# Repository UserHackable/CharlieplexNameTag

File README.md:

## CharlieplexNameTag 

### Board dimensions

* (310000, 240000) original units
* (3.1000, 2.4000) inches
* (78.7400, 60.9600) mm

| Front | Back |
| --- | --- |
|  |  |

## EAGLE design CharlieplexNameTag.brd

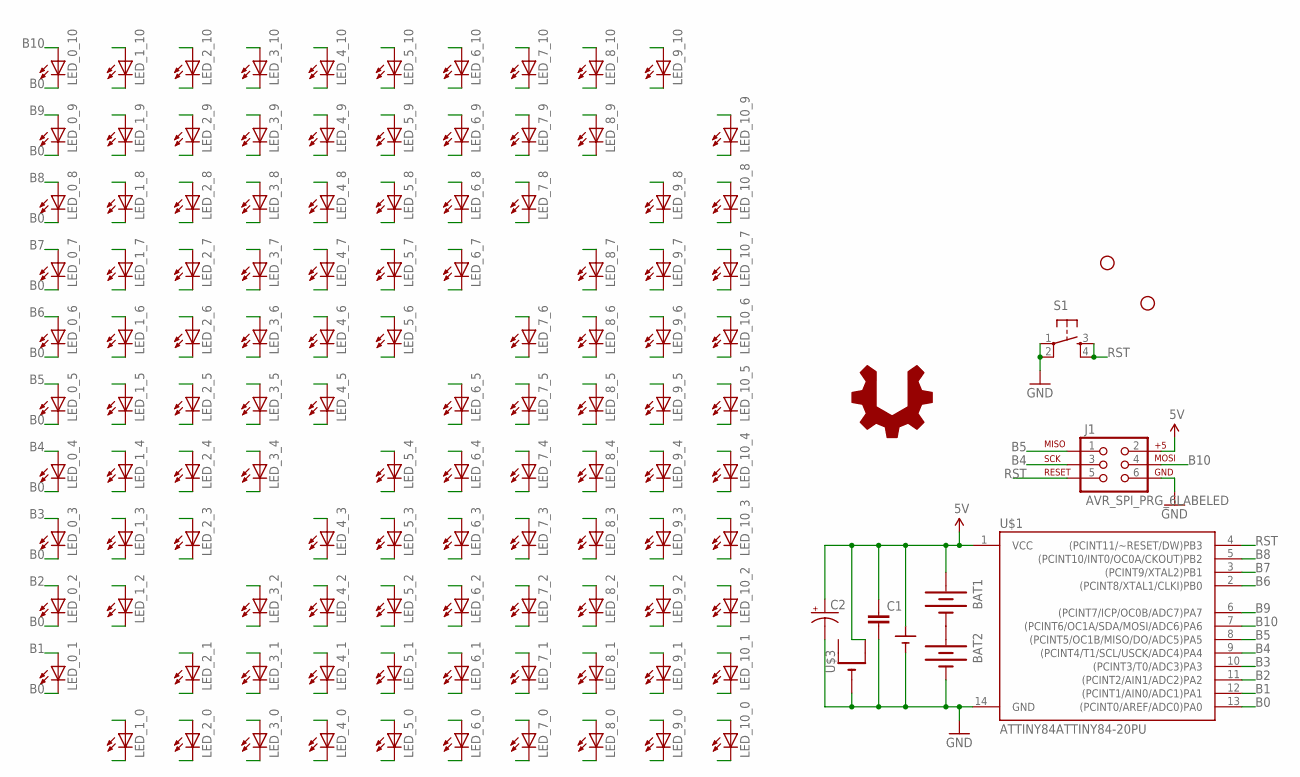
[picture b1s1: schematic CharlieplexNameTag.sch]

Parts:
BAT1, BAT2: BATTERYAAA; BATTERY-AAA
C1: CAPPTH; CAP-PTH-SMALL
C2: CAP_POLPTH1; CPOL-RADIAL-100UF-25V
J1: AVR_SPI_PRG_6LABELED; 2X3-NS
LED_0_1, LED_0_2, LED_0_3, LED_0_4, LED_0_5, LED_0_6, LED_0_7, LED_0_8, LED_0_9, LED_0_10, LED_1_0, LED_1_2, LED_1_3, LED_1_4, LED_1_5, LED_1_6, LED_1_7, LED_1_8, LED_1_9, LED_1_10, LED_2_0, LED_2_1, LED_2_3, LED_2_4, LED_2_5, LED_2_6, LED_2_7, LED_2_8, LED_2_9, LED_2_10, LED_3_0, LED_3_1, LED_3_2, LED_3_4, LED_3_5, LED_3_6, LED_3_7, LED_3_8, LED_3_9, LED_3_10, LED_4_0, LED_4_1, LED_4_2, LED_4_3, LED_4_5, LED_4_6, LED_4_7, LED_4_8, LED_4_9, LED_4_10, LED_5_0, LED_5_1, LED_5_2, LED_5_3, LED_5_4, LED_5_6, LED_5_7, LED_5_8, LED_5_9, LED_5_10, LED_6_0, LED_6_1, LED_6_2, LED_6_3, LED_6_4, LED_6_5, LED_6_7, LED_6_8, LED_6_9, LED_6_10, LED_7_0, LED_7_1, LED_7_2, LED_7_3, LED_7_4, LED_7_5, LED_7_6, LED_7_8, LED_7_9, LED_7_10, LED_8_0, LED_8_1, LED_8_2, LED_8_3, LED_8_4, LED_8_5, LED_8_6, LED_8_7, LED_8_9, LED_8_10, LED_9_0, LED_9_1, LED_9_2, LED_9_3, LED_9_4, LED_9_5, LED_9_6, LED_9_7, LED_9_8, LED_9_10, LED_10_0, LED_10_1, LED_10_2, LED_10_3, LED_10_4, LED_10_5, LED_10_6, LED_10_7, LED_10_8, LED_10_9: LEDOVAL; LED-OVAL
S1: TAC_SWITCHPTH; TACTILE-PTH
STANDOFF1, STANDOFF4: STAND-OFF
U$1: ATTINY84ATTINY84-20PU; DIL14
U$2: BATT2AAA; BC2AAAPC
U$3: CR2032THM; CR2032-THRU
U$4: USER_HACKABLE

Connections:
5V: BAT1.PWR@1 (+), C1.1, C2.1 (+), J1.2 (V+), U$1.1 (VCC), U$2.+, U$3.+2 (+1)
B0: LED_0_1.CATHODE (C), LED_0_2.CATHODE (C), LED_0_3.CATHODE (C), LED_0_4.CATHODE (C), LED_0_5.CATHODE (C), LED_0_6.CATHODE (C), LED_0_7.CATHODE (C), LED_0_8.CATHODE (C), LED_0_9.CATHODE (C), LED_0_10.CATHODE (C), LED_1_0.ANODE (A), LED_2_0.ANODE (A), LED_3_0.ANODE (A), LED_4_0.ANODE (A), LED_5_0.ANODE (A), LED_6_0.ANODE (A), LED_7_0.ANODE (A), LED_8_0.ANODE (A), LED_9_0.ANODE (A), LED_10_0.ANODE (A), U$1.13 ((PCINT0/AREF/ADC0)PA0)
B1: LED_0_1.ANODE (A), LED_1_0.CATHODE (C), LED_1_2.CATHODE (C), LED_1_3.CATHODE (C), LED_1_4.CATHODE (C), LED_1_5.CATHODE (C), LED_1_6.CATHODE (C), LED_1_7.CATHODE (C), LED_1_8.CATHODE (C), LED_1_9.CATHODE (C), LED_1_10.CATHODE (C), LED_2_1.ANODE (A), LED_3_1.ANODE (A), LED_4_1.ANODE (A), LED_5_1.ANODE (A), LED_6_1.ANODE (A), LED_7_1.ANODE (A), LED_8_1.ANODE (A), LED_9_1.ANODE (A), LED_10_1.ANODE (A), U$1.12 ((PCINT1/AIN0/ADC1)PA1)
B2: LED_0_2.ANODE (A), LED_1_2.ANODE (A), LED_2_0.CATHODE (C), LED_2_1.CATHODE (C), LED_2_3.CATHODE (C), LED_2_4.CATHODE (C), LED_2_5.CATHODE (C), LED_2_6.CATHODE (C), LED_2_7.CATHODE (C), LED_2_8.CATHODE (C), LED_2_9.CATHODE (C), LED_2_10.CATHODE (C), LED_3_2.ANODE (A), LED_4_2.ANODE (A), LED_5_2.ANODE (A), LED_6_2.ANODE (A), LED_7_2.ANODE (A), LED_8_2.ANODE (A), LED_9_2.ANODE (A), LED_10_2.ANODE (A), U$1.11 ((PCINT2/AIN1/ADC2)PA2)
B3: LED_0_3.ANODE (A), LED_1_3.ANODE (A), LED_2_3.ANODE (A), LED_3_0.CATHODE (C), LED_3_1.CATHODE (C), LED_3_2.CATHODE (C), LED_3_4.CATHODE (C), LED_3_5.CATHODE (C), LED_3_6.CATHODE (C), LED_3_7.CATHODE (C), LED_3_8.CATHODE (C), LED_3_9.CATHODE (C), LED_3_10.CATHODE (C), LED_4_3.ANODE (A), LED_5_3.ANODE (A), LED_6_3.ANODE (A), LED_7_3.ANODE (A), LED_8_3.ANODE (A), LED_9_3.ANODE (A), LED_10_3.ANODE (A), U$1.10 ((PCINT3/T0/ADC3)PA3)
B4: J1.3 (SCK), LED_0_4.ANODE (A), LED_1_4.ANODE (A), LED_2_4.ANODE (A), LED_3_4.ANODE (A), LED_4_0.CATHODE (C), LED_4_1.CATHODE (C), LED_4_2.CATHODE (C), LED_4_3.CATHODE (C), LED_4_5.CATHODE (C), LED_4_6.CATHODE (C), LED_4_7.CATHODE (C), LED_4_8.CATHODE (C), LED_4_9.CATHODE (C), LED_4_10.CATHODE (C), LED_5_4.ANODE (A), LED_6_4.ANODE (A), LED_7_4.ANODE (A), LED_8_4.ANODE (A), LED_9_4.ANODE (A), LED_10_4.ANODE (A), U$1.9 ((PCINT4/T1/SCL/USCK/ADC4)PA4)
B5: J1.1 (MISO), LED_0_5.ANODE (A), LED_1_5.ANODE (A), LED_2_5.ANODE (A), LED_3_5.ANODE (A), LED_4_5.ANODE (A), LED_5_0.CATHODE (C), LED_5_1.CATHODE (C), LED_5_2.CATHODE (C), LED_5_3.CATHODE (C), LED_5_4.CATHODE (C), LED_5_6.CATHODE (C), LED_5_7.CATHODE (C), LED_5_8.CATHODE (C), LED_5_9.CATHODE (C), LED_5_10.CATHODE (C), LED_6_5.ANODE (A), LED_7_5.ANODE (A), LED_8_5.ANODE (A), LED_9_5.ANODE (A), LED_10_5.ANODE (A), U$1.8 ((PCINT5/OC1B/MISO/DO/ADC5)PA5)
B6: LED_0_6.ANODE (A), LED_1_6.ANODE (A), LED_2_6.ANODE (A), LED_3_6.ANODE (A), LED_4_6.ANODE (A), LED_5_6.ANODE (A), LED_6_0.CATHODE (C), LED_6_1.CATHODE (C), LED_6_2.CATHODE (C), LED_6_3.CATHODE (C), LED_6_4.CATHODE (C), LED_6_5.CATHODE (C), LED_6_7.CATHODE (C), LED_6_8.CATHODE (C), LED_6_9.CATHODE (C), LED_6_10.CATHODE (C), LED_7_6.ANODE (A), LED_8_6.ANODE (A), LED_9_6.ANODE (A), LED_10_6.ANODE (A), U$1.2 ((PCINT8/XTAL1/CLKI)PB0)
B7: LED_0_7.ANODE (A), LED_1_7.ANODE (A), LED_2_7.ANODE (A), LED_3_7.ANODE (A), LED_4_7.ANODE (A), LED_5_7.ANODE (A), LED_6_7.ANODE (A), LED_7_0.CATHODE (C), LED_7_1.CATHODE (C), LED_7_2.CATHODE (C), LED_7_3.CATHODE (C), LED_7_4.CATHODE (C), LED_7_5.CATHODE (C), LED_7_6.CATHODE (C), LED_7_8.CATHODE (C), LED_7_9.CATHODE (C), LED_7_10.CATHODE (C), LED_8_7.ANODE (A), LED_9_7.ANODE (A), LED_10_7.ANODE (A), U$1.3 ((PCINT9/XTAL2)PB1)
B8: LED_0_8.ANODE (A), LED_1_8.ANODE (A), LED_2_8.ANODE (A), LED_3_8.ANODE (A), LED_4_8.ANODE (A), LED_5_8.ANODE (A), LED_6_8.ANODE (A), LED_7_8.ANODE (A), LED_8_0.CATHODE (C), LED_8_1.CATHODE (C), LED_8_2.CATHODE (C), LED_8_3.CATHODE (C), LED_8_4.CATHODE (C), LED_8_5.CATHODE (C), LED_8_6.CATHODE (C), LED_8_7.CATHODE (C), LED_8_9.CATHODE (C), LED_8_10.CATHODE (C), LED_9_8.ANODE (A), LED_10_8.ANODE (A), U$1.5 ((PCINT10/INT0/OC0A/CKOUT)PB2)
B9: LED_0_9.ANODE (A), LED_1_9.ANODE (A), LED_2_9.ANODE (A), LED_3_9.ANODE (A), LED_4_9.ANODE (A), LED_5_9.ANODE (A), LED_6_9.ANODE (A), LED_7_9.ANODE (A), LED_8_9.ANODE (A), LED_9_0.CATHODE (C), LED_9_1.CATHODE (C), LED_9_2.CATHODE (C), LED_9_3.CATHODE (C), LED_9_4.CATHODE (C), LED_9_5.CATHODE (C), LED_9_6.CATHODE (C), LED_9_7.CATHODE (C), LED_9_8.CATHODE (C), LED_9_10.CATHODE (C), LED_10_9.ANODE (A), U$1.6 ((PCINT7/ICP/OC0B/ADC7)PA7)
B10: J1.4 (MOSI), LED_0_10.ANODE (A), LED_1_10.ANODE (A), LED_2_10.ANODE (A), LED_3_10.ANODE (A), LED_4_10.ANODE (A), LED_5_10.ANODE (A), LED_6_10.ANODE (A), LED_7_10.ANODE (A), LED_8_10.ANODE (A), LED_9_10.ANODE (A), LED_10_0.CATHODE (C), LED_10_1.CATHODE (C), LED_10_2.CATHODE (C), LED_10_3.CATHODE (C), LED_10_4.CATHODE (C), LED_10_5.CATHODE (C), LED_10_6.CATHODE (C), LED_10_7.CATHODE (C), LED_10_8.CATHODE (C), LED_10_9.CATHODE (C), U$1.7 ((PCINT6/OC1A/SDA/MOSI/ADC6)PA6)
GND: BAT2.GND@1 (-), C1.2, C2.2 (-), J1.6 (GND), S1.1, S1.2, U$1.14 (GND), U$2.-, U$3.-
unnamed: BAT1.GND@1 (-), BAT2.PWR@1 (+)
RST: J1.5 (RST), S1.3, S1.4, U$1.4 ((PCINT11/~RESET/DW)PB3)

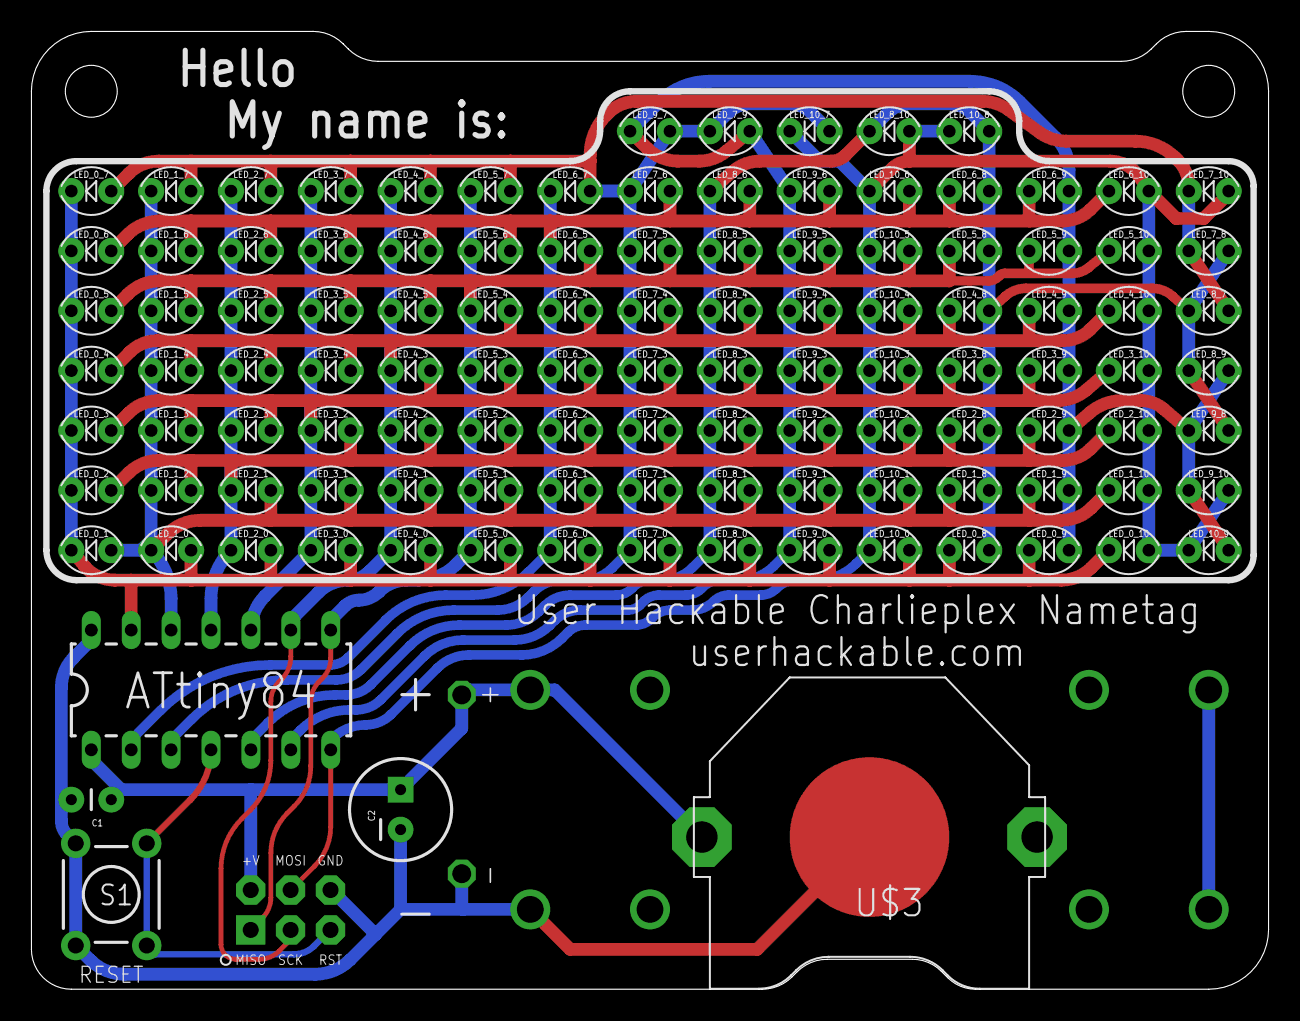
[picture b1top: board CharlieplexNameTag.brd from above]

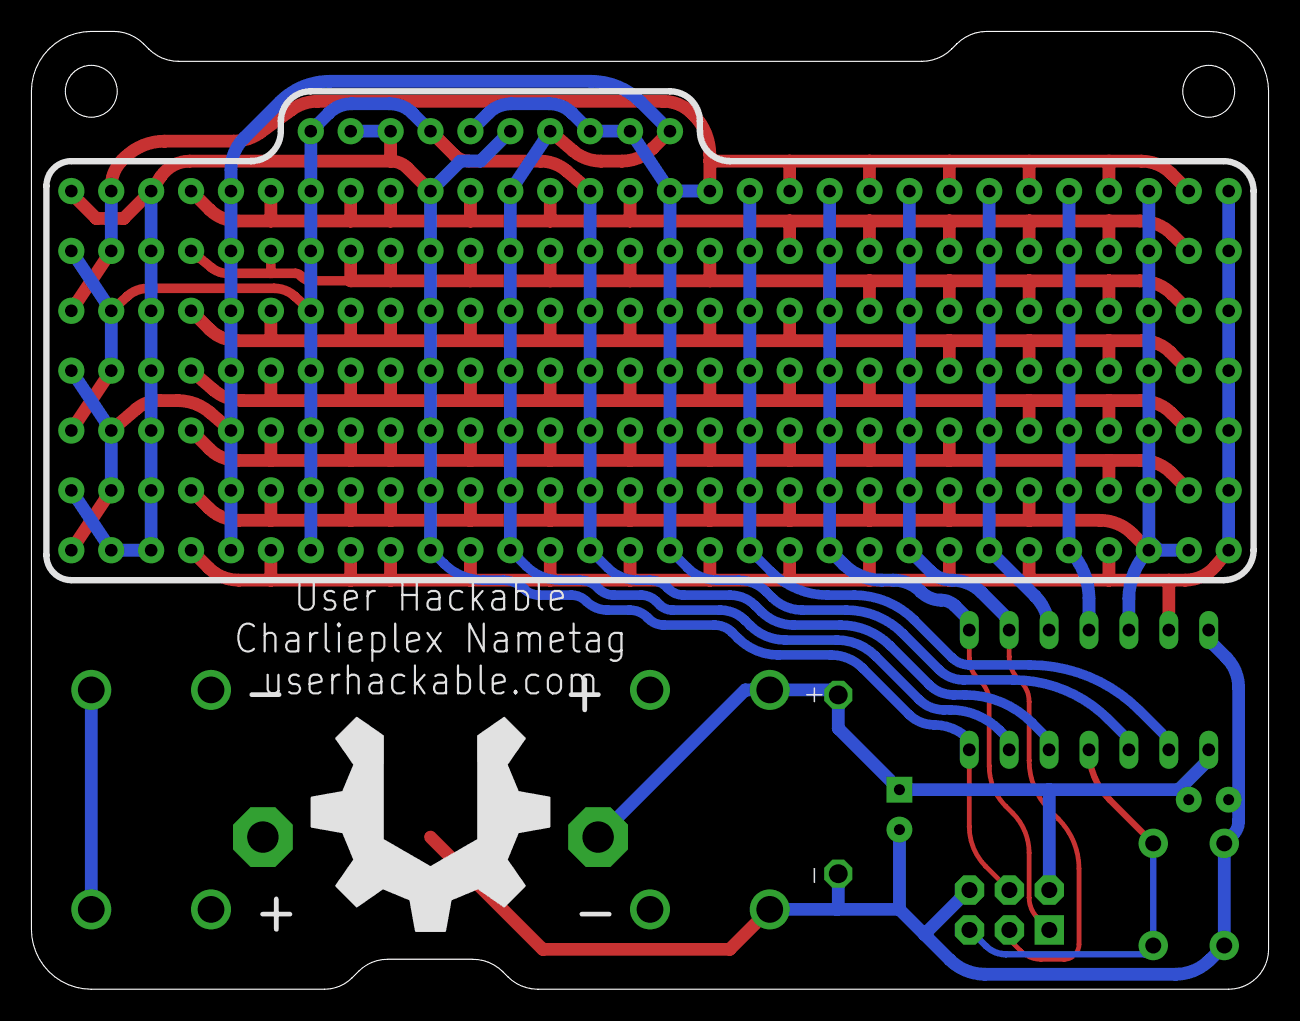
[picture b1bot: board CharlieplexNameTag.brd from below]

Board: 2 copper layers, 78.7 x 61.0 mm, 122 parts (4 on the bottom side), 15 nets.

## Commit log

2016-04-07 from Makefile

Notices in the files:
parts and their libraries:
SparkFun-DigitalIC: Licensing: Creative Commons ShareAlike 4.0 International - https://creativecommons.org/licenses/by-sa/4.0
